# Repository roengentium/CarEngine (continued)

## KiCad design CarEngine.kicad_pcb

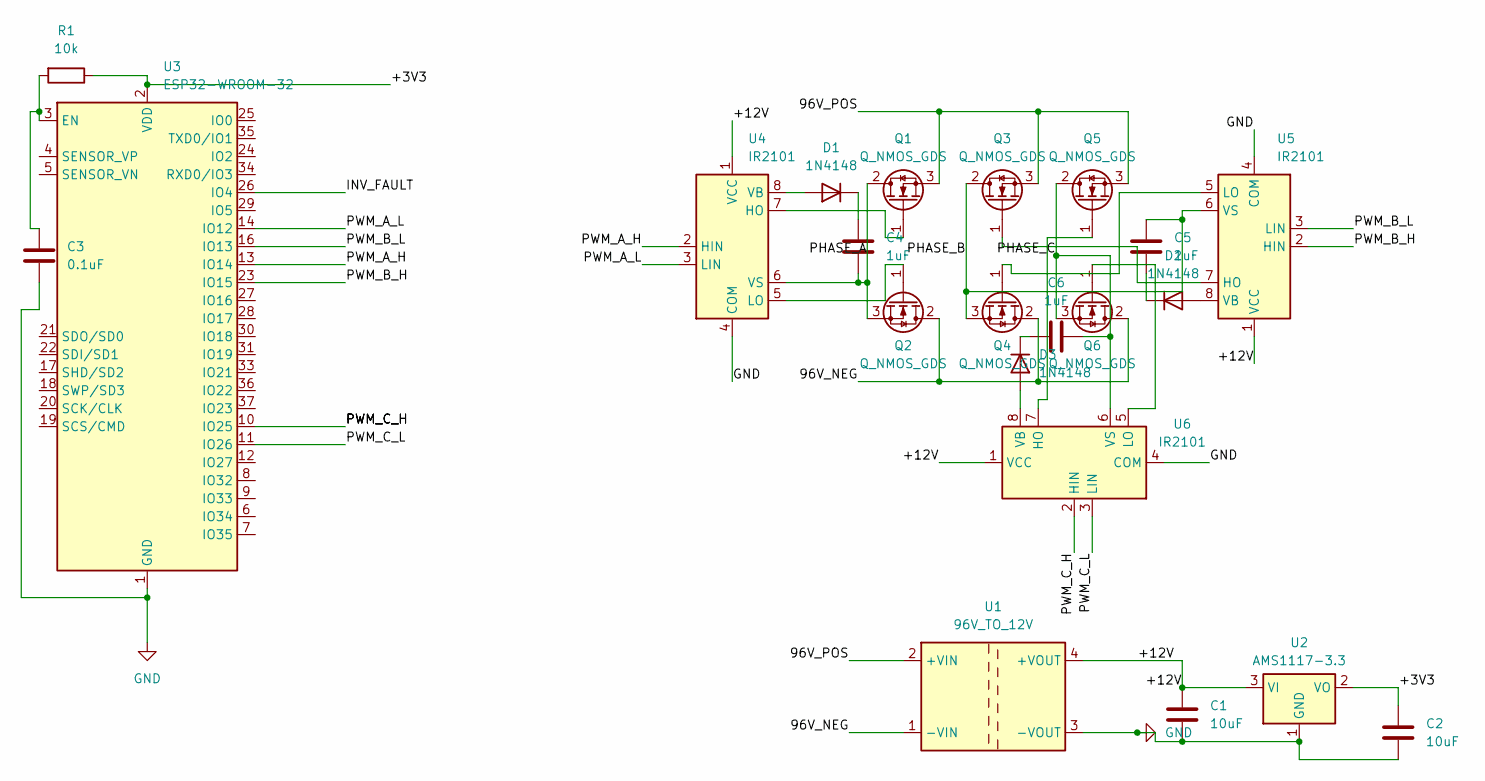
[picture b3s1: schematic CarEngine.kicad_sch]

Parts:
C1, C2: 10uF; SOT-223-3_TabPin2
C3: 0.1uF; C_Disc_D3.0mm_W1.6mm_P2.50mm
C4, C5, C6: 1uF; D_DO-35_SOD27_P7.62mm_Horizontal
D1, D2, D3: 1N4148; D_DO-35_SOD27_P7.62mm_Horizontal
Q1, Q2, Q3, Q4, Q5, Q6: Q_NMOS_GDS; TO-220-3_Vertical
R1: 10k; R_Axial_DIN0207_L6.3mm_D2.5mm_P7.62mm_Horizontal
U1: 96V_TO_12V; Converter_DCDC_Murata_CRE1xxxxxxSC_THT
U2: AMS1117-3.3; SOT-223-3_TabPin2
U3: ESP32-WROOM-32
U4, U5, U6: IR2101; DIP-8_W7.62mm

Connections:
/96V_NEG: Q2.2 (D), Q4.2 (D), Q6.2 (D), U1.1 (-VIN)
/96V_POS: Q1.3 (S), Q3.3 (S), Q5.3 (S), U1.2 (+VIN)
/+3V3: C2.1, R1.1, U2.2 (VO), U3.2 (VDD)
/+12V: C1.2, U1.4 (+VOUT), U2.3 (VI), U4.1 (VCC), U5.1 (VCC), U6.1 (VCC)
/INV_FAULT: U3.26 (IO4)
/PHASE_A: C4.1, Q1.2 (D), Q2.3 (S), U4.6 (VS)
/PHASE_B: C5.2, Q3.2 (D), Q4.3 (S), U5.6 (VS)
/PHASE_C: C6.2, Q5.2 (D), Q6.3 (S), U6.6 (VS)
/PWM_A_H: U3.13 (IO14), U4.2 (HIN)
/PWM_A_L: U3.14 (IO12), U4.3 (LIN)
/PWM_B_H: U3.23 (IO15), U5.2 (HIN)
/PWM_B_L: U3.16 (IO13), U5.3 (LIN)
/PWM_C_H: U3.10 (IO25), U6.2 (HIN)
/PWM_C_L: U3.11 (IO26), U6.3 (LIN)
GND: C1.1, C2.2, C3.2, U1.3 (-VOUT), U2.1 (GND), U3.1 (GND), U3.15 (GND), U3.38 (GND), U3.39 (GND), U4.4 (COM), U5.4 (COM), U6.4 (COM)
unnamed: D1.2 (A), U4.8 (VB)
unnamed: C4.2, D1.1 (K)
unnamed: D2.2 (A), U5.8 (VB)
unnamed: C5.1, D2.1 (K)
unnamed: D3.2 (A), U6.8 (VB)
unnamed: C6.1, D3.1 (K)
unnamed: Q1.1 (G), U4.7 (HO)
unnamed: Q2.1 (G), U4.5 (LO)
unnamed: Q3.1 (G), U5.7 (HO)
unnamed: Q4.1 (G), U5.5 (LO)
unnamed: Q5.1 (G), U6.7 (HO)
unnamed: Q6.1 (G), U6.5 (LO)
unnamed: C3.1, R1.2, U3.3 (EN)

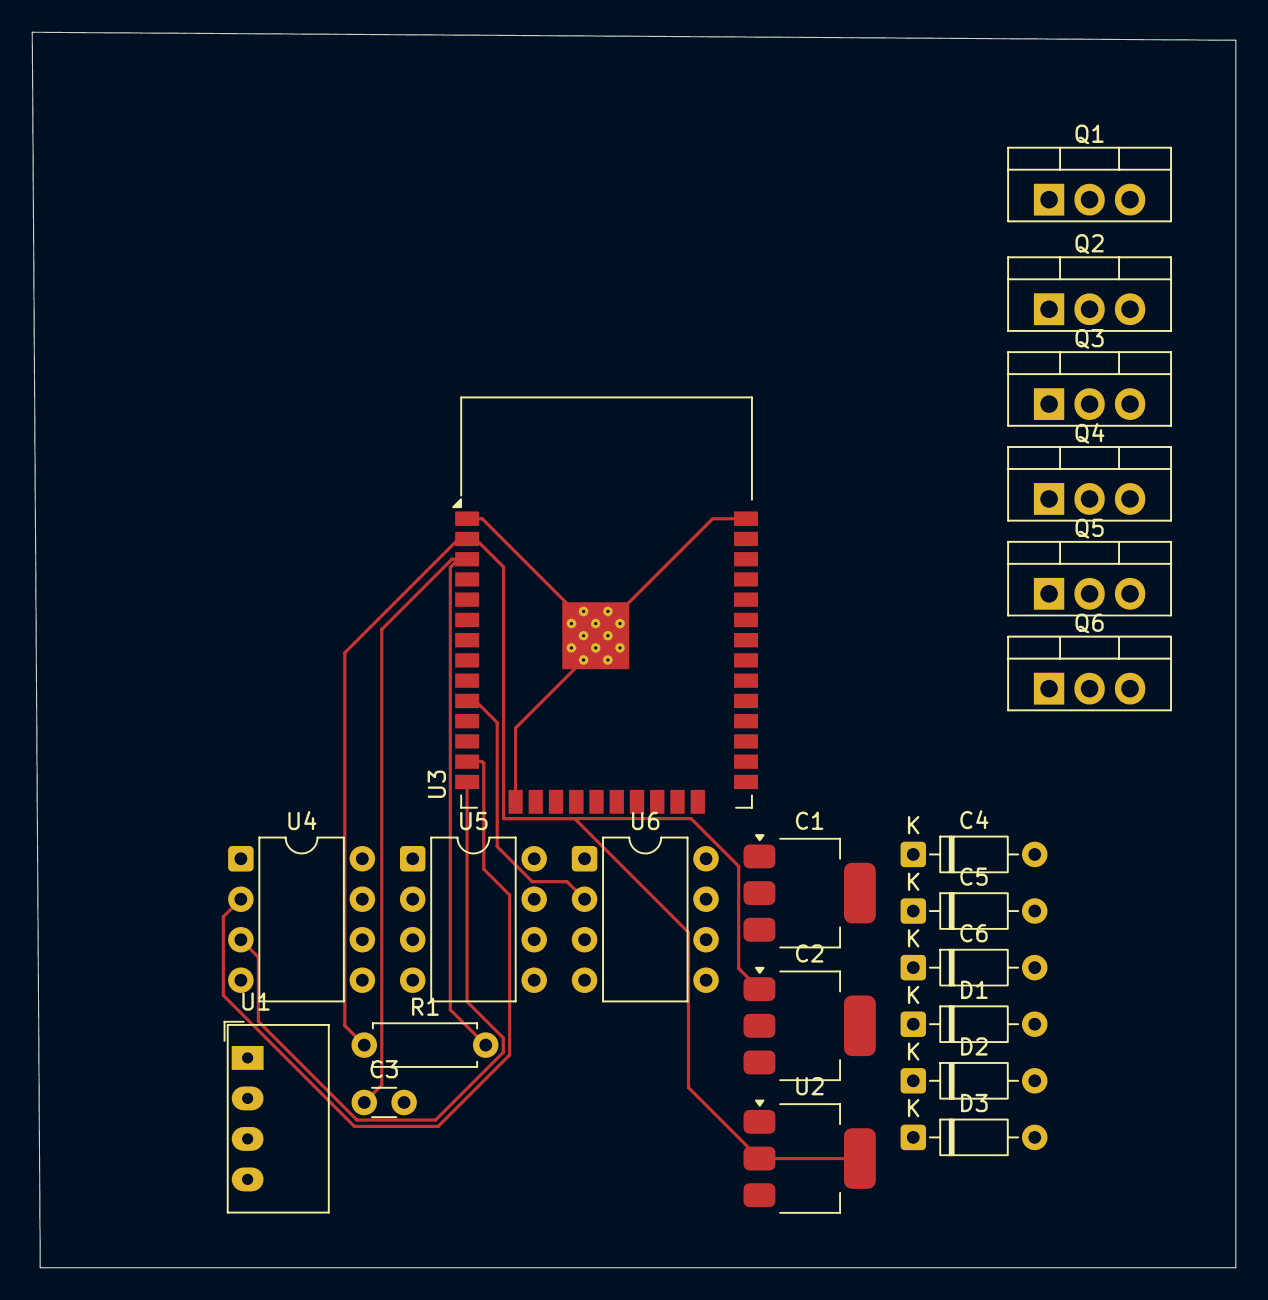
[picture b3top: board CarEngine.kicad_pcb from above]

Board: 2 copper layers, 75.5 x 77.5 mm, 22 parts (0 on the bottom side), 27 nets.

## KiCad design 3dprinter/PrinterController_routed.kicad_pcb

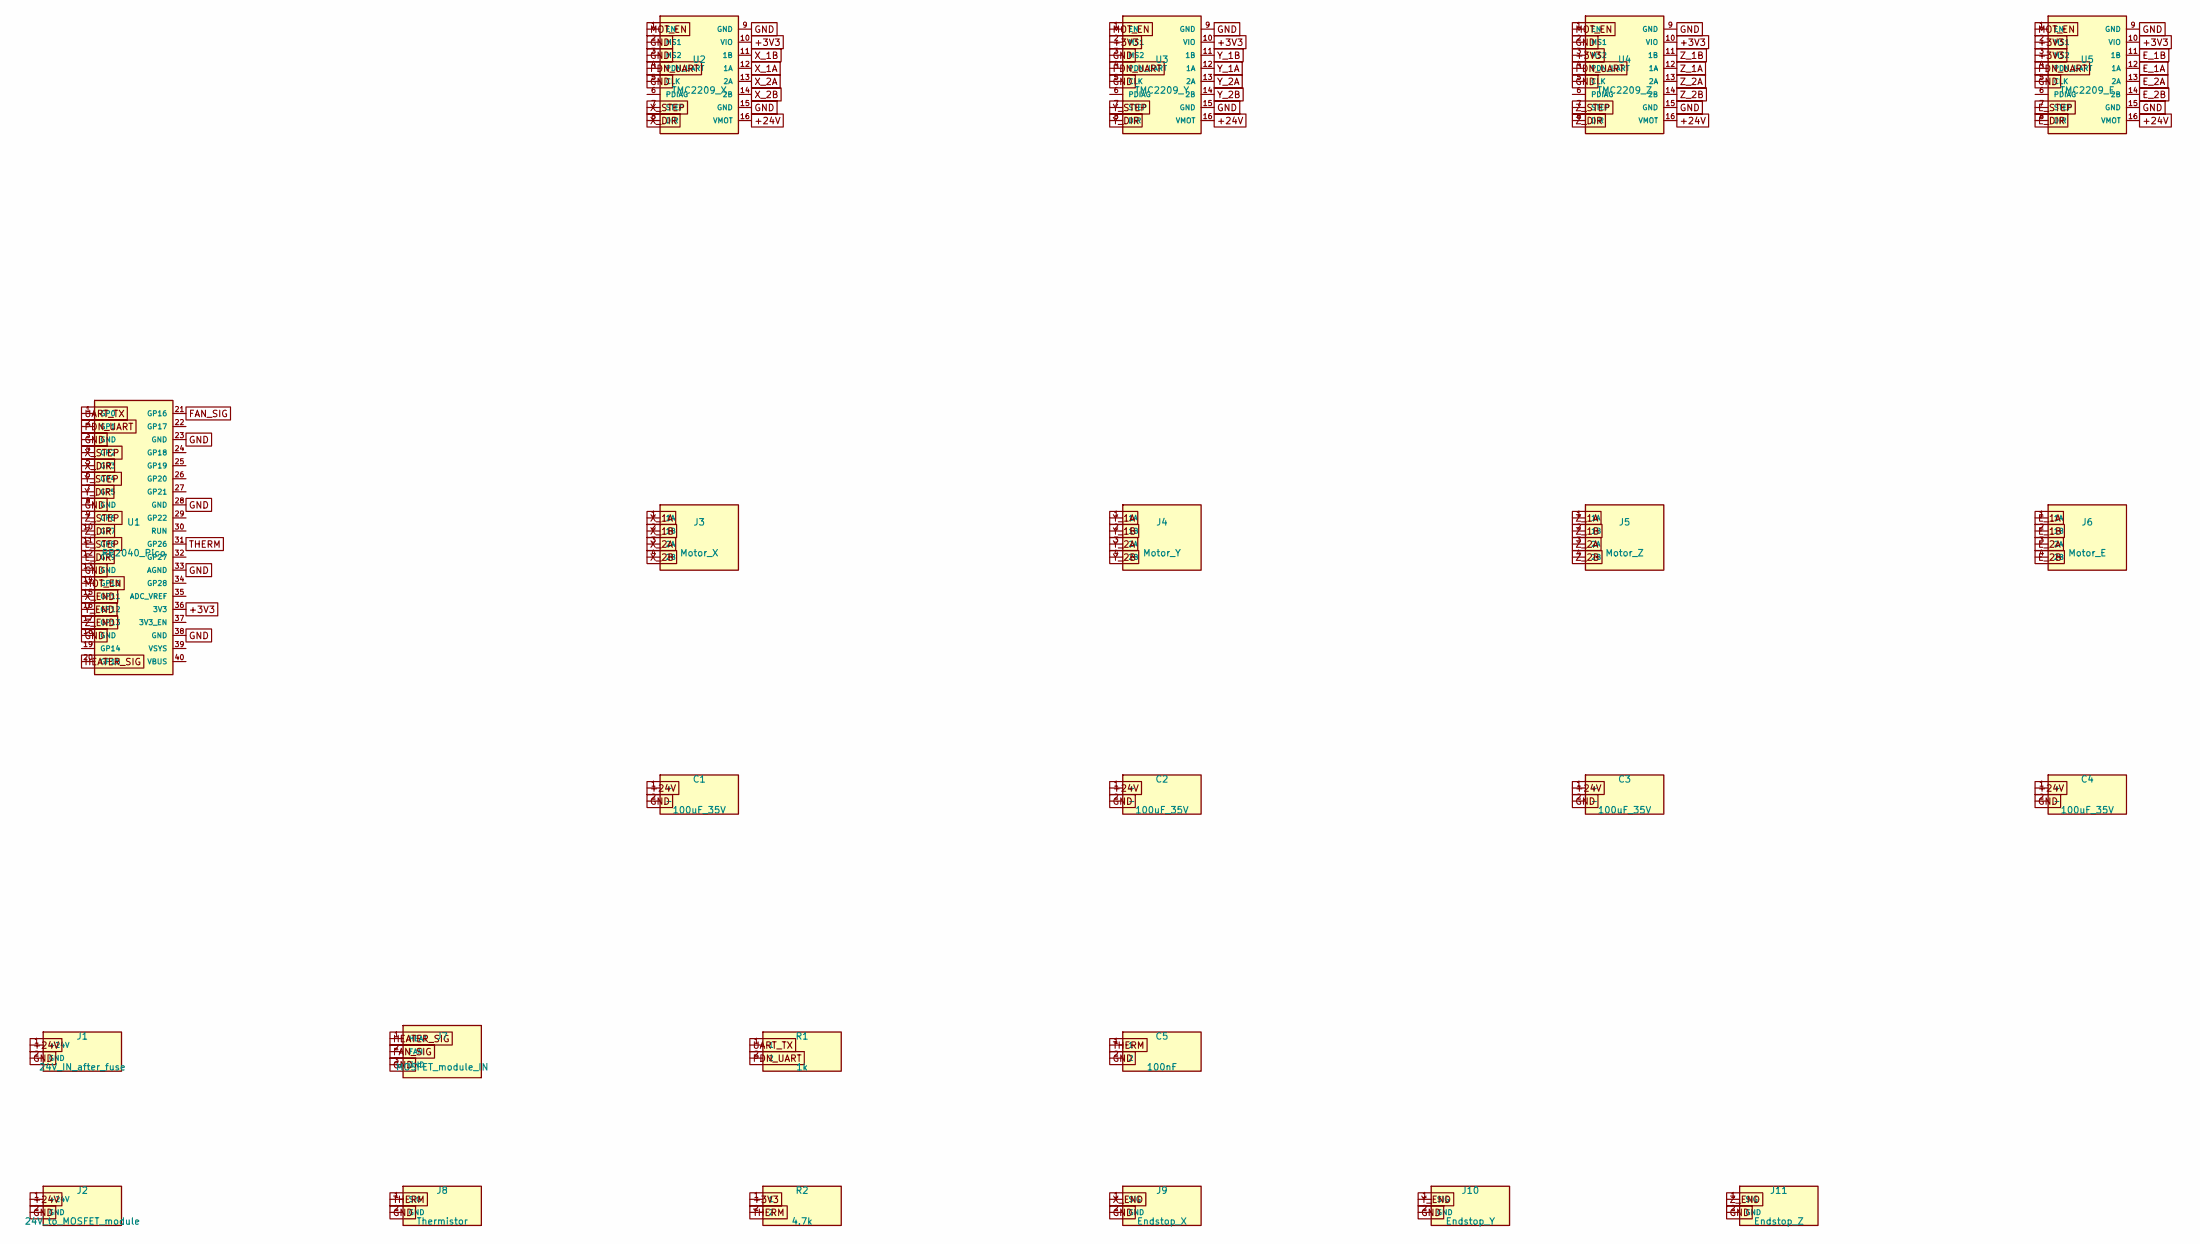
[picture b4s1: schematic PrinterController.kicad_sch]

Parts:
C1, C2, C3, C4: 100uF_35V; CP_Radial_D6.3mm_P2.50mm
C5: 100nF; C_Disc_D3.0mm_W1.6mm_P2.50mm
J1: 24V_IN_after_fuse; TerminalBlock_bornier-2_P5.08mm
J2: 24V_to_MOSFET_module; TerminalBlock_bornier-2_P5.08mm
J3: Motor_X; PinHeader_1x04_P2.54mm_Vertical
J4: Motor_Y; PinHeader_1x04_P2.54mm_Vertical
J5: Motor_Z; PinHeader_1x04_P2.54mm_Vertical
J6: Motor_E; PinHeader_1x04_P2.54mm_Vertical
J7: MOSFET_module_IN; PinHeader_1x03_P2.54mm_Vertical
J8: Thermistor; PinHeader_1x02_P2.54mm_Vertical
J9: Endstop_X; PinHeader_1x02_P2.54mm_Vertical
J10: Endstop_Y; PinHeader_1x02_P2.54mm_Vertical
J11: Endstop_Z; PinHeader_1x02_P2.54mm_Vertical
R1: 1k; R_Axial_DIN0207_L6.3mm_D2.5mm_P7.62mm_Horizontal
R2: 4.7k; R_Axial_DIN0207_L6.3mm_D2.5mm_P7.62mm_Horizontal
U1: RP2040_Pico; RaspberryPi_Pico_Common_THT
U2: TMC2209_X; Pololu_Breakout-16_15.2x20.3mm
U3: TMC2209_Y; Pololu_Breakout-16_15.2x20.3mm
U4: TMC2209_Z; Pololu_Breakout-16_15.2x20.3mm
U5: TMC2209_E; Pololu_Breakout-16_15.2x20.3mm

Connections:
+3V3: R2.1, U1.36 (3V3), U2.10 (VIO), U3.2 (MS1), U3.10 (VIO), U4.3 (MS2), U4.10 (VIO), U5.2 (MS1), U5.3 (MS2), U5.10 (VIO)
+24V: C1.1 (+), C2.1 (+), C3.1 (+), C4.1 (+), J1.1 (+24V), J2.1 (+24V), U2.16 (VMOT), U3.16 (VMOT), U4.16 (VMOT), U5.16 (VMOT)
E_1A: J6.1 (1A), U5.12 (1A)
E_1B: J6.2 (1B), U5.11 (1B)
E_2A: J6.3 (2A), U5.13 (2A)
E_2B: J6.4 (2B), U5.14 (2B)
E_DIR: U1.12 (GP9), U5.8 (DIR)
E_STEP: U1.11 (GP8), U5.7 (STEP)
FAN_SIG: J7.2 (FAN), U1.21 (GP16)
GND: C1.2 (-), C2.2 (-), C3.2 (-), C4.2 (-), C5.2, J1.2 (GND), J2.2 (GND), J7.3 (GND), J8.2 (GND), J9.2 (GND), J10.2 (GND), J11.2 (GND), U1.3 (GND), U1.8 (GND), U1.13 (GND), U1.18 (GND), U1.23 (GND), U1.28 (GND), U1.33 (AGND), U1.38 (GND), U2.2 (MS1), U2.3 (MS2), U2.5 (CLK), U2.9 (GND), U2.15 (GND), U3.3 (MS2), U3.5 (CLK), U3.9 (GND), U3.15 (GND), U4.2 (MS1), U4.5 (CLK), U4.9 (GND), U4.15 (GND), U5.5 (CLK), U5.9 (GND), U5.15 (GND)
HEATER_SIG: J7.1 (HEAT), U1.20 (GP15)
MOT_EN: U1.14 (GP10), U2.1 (EN), U3.1 (EN), U4.1 (EN), U5.1 (EN)
PDN_UART: R1.2, U1.2 (GP1), U2.4 (PDN_UART), U3.4 (PDN_UART), U4.4 (PDN_UART), U5.4 (PDN_UART)
THERM: C5.1, J8.1 (SIG), R2.2, U1.31 (GP26)
UART_TX: R1.1, U1.1 (GP0)
X_1A: J3.1 (1A), U2.12 (1A)
X_1B: J3.2 (1B), U2.11 (1B)
X_2A: J3.3 (2A), U2.13 (2A)
X_2B: J3.4 (2B), U2.14 (2B)
X_DIR: U1.5 (GP3), U2.8 (DIR)
X_END: J9.1 (SIG), U1.15 (GP11)
X_STEP: U1.4 (GP2), U2.7 (STEP)
Y_1A: J4.1 (1A), U3.12 (1A)
Y_1B: J4.2 (1B), U3.11 (1B)
Y_2A: J4.3 (2A), U3.13 (2A)
Y_2B: J4.4 (2B), U3.14 (2B)
Y_DIR: U1.7 (GP5), U3.8 (DIR)
Y_END: J10.1 (SIG), U1.16 (GP12)
Y_STEP: U1.6 (GP4), U3.7 (STEP)
Z_1A: J5.1 (1A), U4.12 (1A)
Z_1B: J5.2 (1B), U4.11 (1B)
Z_2A: J5.3 (2A), U4.13 (2A)
Z_2B: J5.4 (2B), U4.14 (2B)
Z_DIR: U1.10 (GP7), U4.8 (DIR)
Z_END: J11.1 (SIG), U1.17 (GP13)
Z_STEP: U1.9 (GP6), U4.7 (STEP)

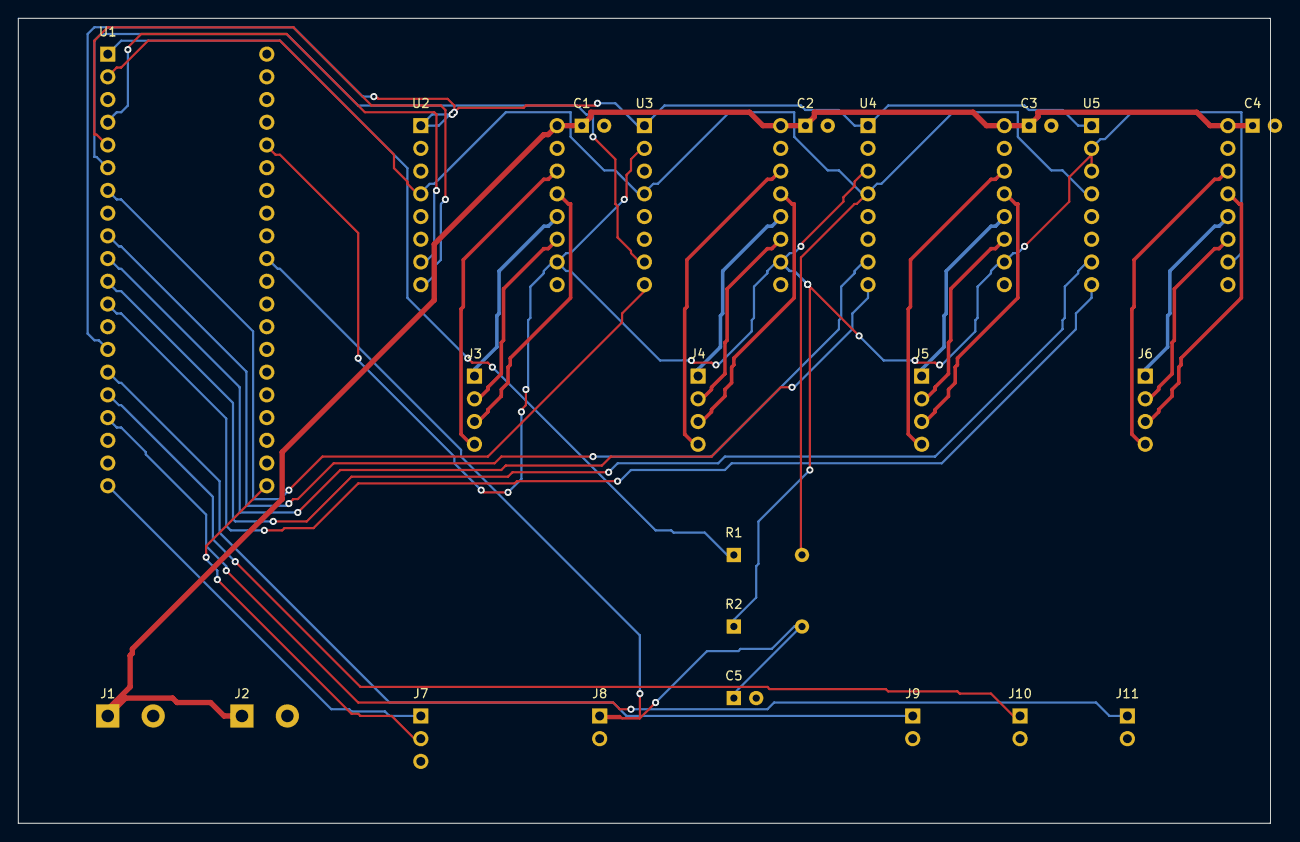
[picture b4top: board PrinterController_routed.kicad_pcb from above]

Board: 2 copper layers, 140.0 x 90.0 mm, 23 parts (0 on the bottom side), 36 nets.

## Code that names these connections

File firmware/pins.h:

// Pin map for the 14 V isolated DC-DC controller (ESP32 DevKitC-style module, U1).
// Matches converter_*/…kicad_sch net labels. Firmware itself is NOT included/tested.
#pragma once
#define PIN_PWM_AH   25   // UCC21520 U2 INA  -> Q1 (leg A high side)
#define PIN_PWM_AL   26   // UCC21520 U2 INB  -> Q2 (leg A low side)
#define PIN_PWM_BH   27   // UCC21520 U3 INA  -> Q3 (leg B high side)
#define PIN_PWM_BL   14   // UCC21520 U3 INB  -> Q4 (leg B low side)
#define PIN_SR1      32   // sync-rectifier 1 (via UCC27524 U4)
#define PIN_SR2      33   // sync-rectifier 2
#define PIN_VSENSE   34   // ADC1, 14 V via 47k/10k divider
#define PIN_ISENSE   35   // ADC1, INA180A1 output
#define PIN_TSENSE   36   // ADC1, 10k NTC divider
#define PIN_OCP_N    39   // input: LOW = hardware over-current tripped
#define PIN_DRV_EN   13   // output: HIGH = request drivers enabled (OCP can still override)
// Scaling
#define VSENSE_DIV   (10.0f/(47.0f+10.0f))     // Vout = Vadc / VSENSE_DIV
#define ISENSE_V_PER_A (0.002f*20.0f)          // 2 mohm shunt x 20 V/V = 0.04 V/A
#define OCP_TRIP_V   (3.3f*10.0f/(8.2f+10.0f)) // ~1.81 V  => ~45 A
// IMPORTANT: UCC21520 dead time is set by RDT (20k => ~200 ns, check datasheet); never tie DT to VCCI.
